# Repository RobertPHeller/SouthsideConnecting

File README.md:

# Southside Connecting

This is an XTrkCAD  version of Railroad C:  "Southside  Connecting"  from "Six
Atlas HO  Railroads  You Can Build",  Atlas book #13, 2nd  edition, by John H.
Armstrong and Thaddeus Stepok.

This plan is slightly adjusted from the original and uses flextrack

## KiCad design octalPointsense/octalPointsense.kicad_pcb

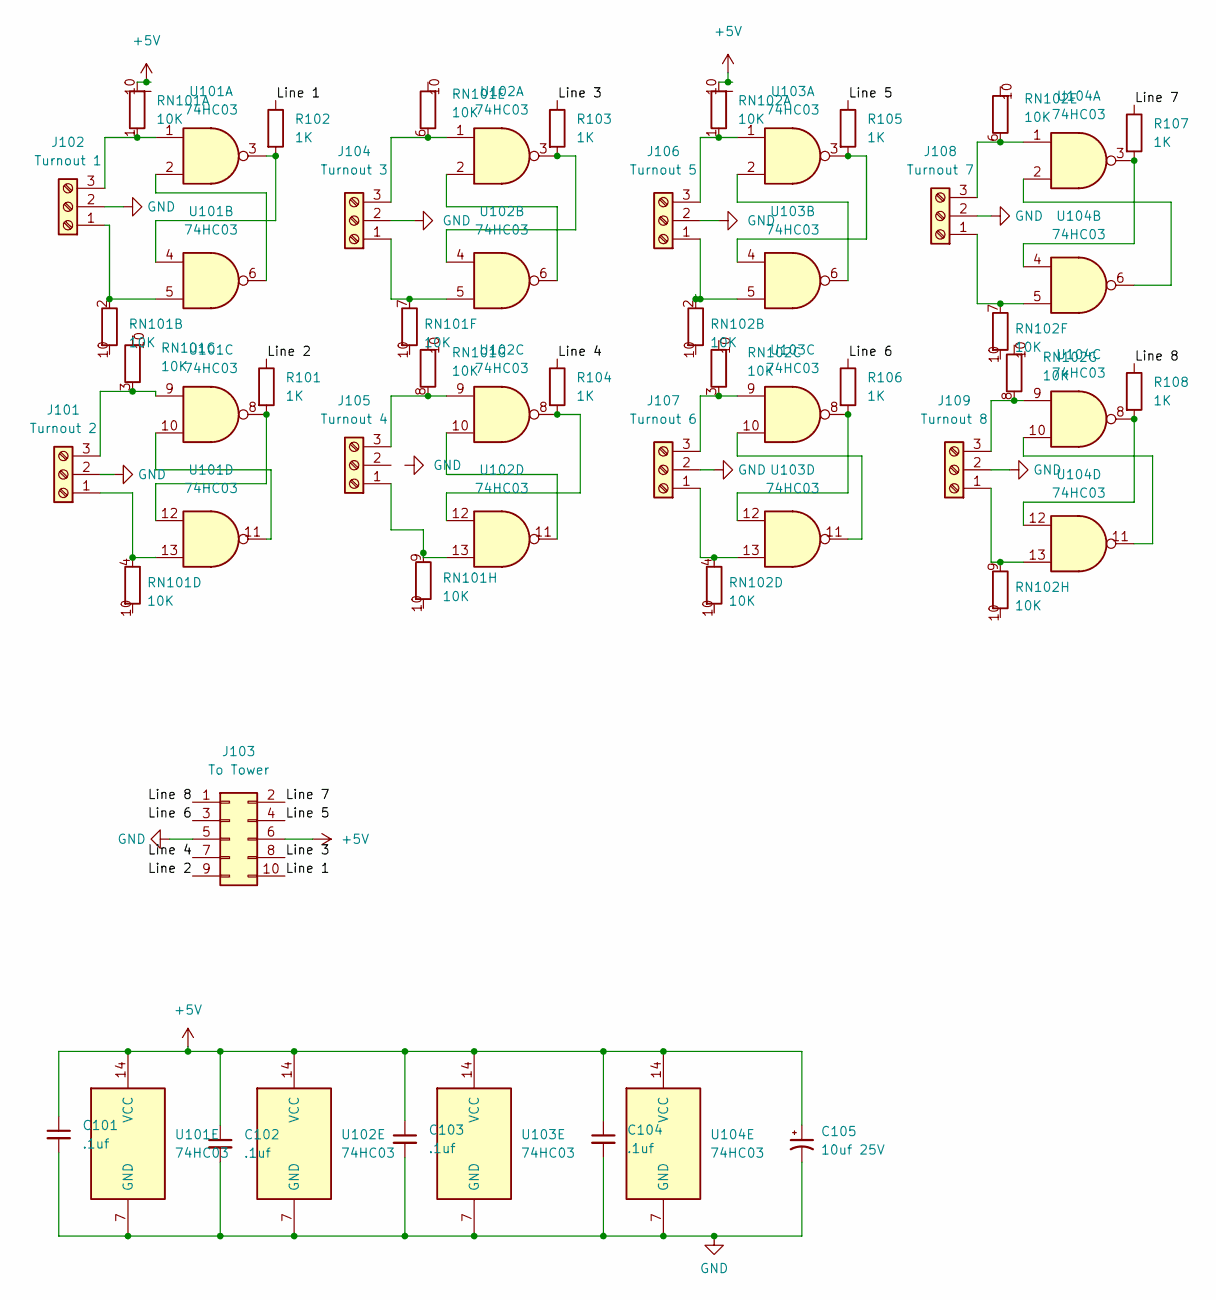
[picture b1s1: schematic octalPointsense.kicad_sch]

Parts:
C101, C102, C103, C104: .1uf; C_0603_1608Metric; Mouser Part Number 603-C0603ZRY5V8BB104
C105: 10uf 25V; CP_Elec_4x5.4; Mouser Part Number 80-EDH106M025A9BAA
J101: Turnout 2; TerminalBlock_TE_282834-3_1x03_P2.54mm_Horizontal
J102: Turnout 1; TerminalBlock_TE_282834-3_1x03_P2.54mm_Horizontal
J103: To Tower; PinHeader_2x05_P2.54mm_Vertical
J104: Turnout 3; TerminalBlock_TE_282834-3_1x03_P2.54mm_Horizontal
J105: Turnout 4; TerminalBlock_TE_282834-3_1x03_P2.54mm_Horizontal
J106: Turnout 5; TerminalBlock_TE_282834-3_1x03_P2.54mm_Horizontal
J107: Turnout 6; TerminalBlock_TE_282834-3_1x03_P2.54mm_Horizontal
J108: Turnout 7; TerminalBlock_TE_282834-3_1x03_P2.54mm_Horizontal
J109: Turnout 8; TerminalBlock_TE_282834-3_1x03_P2.54mm_Horizontal
R101, R102, R103, R104, R105, R106, R107, R108: 1K; R_0603_1608Metric; Mouser Part Number 603-RT0603BRD131KL
RN101, RN102: 10K; YC158TJR0710KL; Mouser Part Number 603-YC158TJR-0710KL
U101, U102, U103, U104: 74HC03; TSSOP-14_4.4x5mm_P0.65mm; Mouser Part Number 771-HC03PW118

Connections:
+5V: C101.1, C102.1, C103.1, C104.1, C105.1, J103.6, RN101.5 (common), RN101.10 (R1.1), RN102.5 (common), RN102.10 (R1.1), U101.14 (VCC), U102.14 (VCC), U103.14 (VCC), U104.14 (VCC)
/Line 1: J103.10, R102.1
/Line 2: J103.9, R101.1
/Line 3: J103.8, R103.1
/Line 4: J103.7, R104.1
/Line 5: J103.4, R105.1
/Line 6: J103.3, R106.1
/Line 7: J103.2, R107.1
/Line 8: J103.1, R108.1
GND: C101.2, C102.2, C103.2, C104.2, C105.2, J101.2, J102.2, J103.5, J104.2, J106.2, J107.2, J108.2, J109.2, U101.7 (GND), U102.7 (GND), U103.7 (GND), U104.7 (GND)
unnamed: J101.1, RN101.4 (R4.2), U101.13
unnamed: J101.3, RN101.3 (R3.2), U101.9
unnamed: J102.1, RN101.2 (R2.2), U101.5
unnamed: J102.3, RN101.1 (R1.2), U101.1
unnamed: J104.1, RN101.7 (R6.2), U102.5
unnamed: J104.3, RN101.6 (R5.2), U102.1
unnamed: J105.1, RN101.9 (R8.2), U102.13
unnamed: J105.3, RN101.8 (R7.2), U102.9
unnamed: J106.1, RN102.2 (R2.2), U103.5
unnamed: J106.3, RN102.1 (R1.2), U103.1
unnamed: J107.1, RN102.4 (R4.2), U103.13
unnamed: J107.3, RN102.3 (R3.2), U103.9
unnamed: J108.1, RN102.7 (R6.2), U104.5
unnamed: J108.3, RN102.6 (R5.2), U104.1
unnamed: J109.1, RN102.9 (R8.2), U104.13
unnamed: J109.3, RN102.8 (R7.2), U104.9
unnamed: U101.2, U101.6
unnamed: R102.2, U101.3, U101.4
unnamed: U101.10, U101.11
unnamed: R101.2, U101.8, U101.12
unnamed: U102.2, U102.6
unnamed: R103.2, U102.3, U102.4
unnamed: U102.10, U102.11
unnamed: R104.2, U102.8, U102.12
unnamed: U103.2, U103.6
unnamed: R105.2, U103.3, U103.4
unnamed: U103.10, U103.11
unnamed: R106.2, U103.8, U103.12
unnamed: U104.2, U104.6
unnamed: R107.2, U104.3, U104.4
unnamed: R108.2, U104.8, U104.12
unnamed: U104.10, U104.11

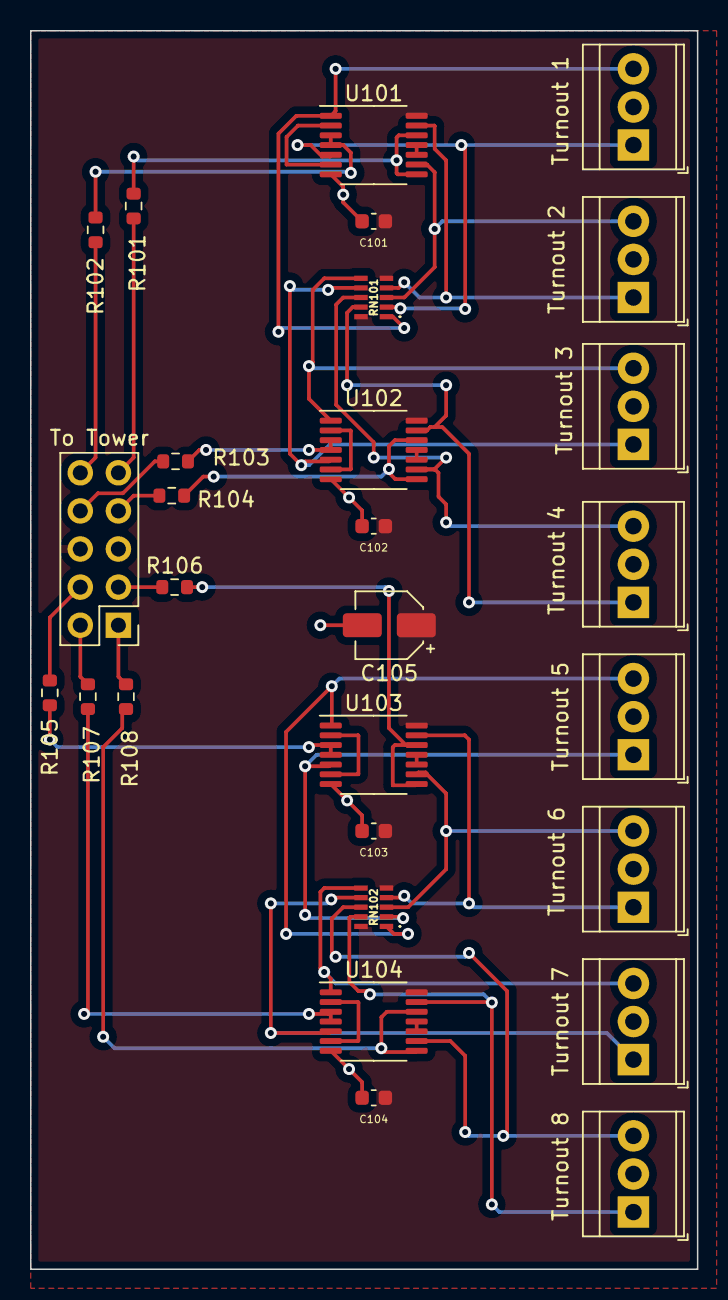
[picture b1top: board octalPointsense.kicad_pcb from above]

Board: 2 copper layers, 44.5 x 82.6 mm, 28 parts (0 on the bottom side), 42 nets.
